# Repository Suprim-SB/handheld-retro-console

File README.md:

# HANDHELD RETRO CONSOLE
A diy handheld retro console that is built to be simple, cheap and small. It includes classic retro games that you can play to spend your time!
<br> 
<br>
<br>

# WHAT IS IT?
A handheld console is a game device meant to fit in the palm of your hands!. Although they are not as powerful as traditional consoles, they are quite nice to help you pass your free time instead of just doomscrolling. And with how everyone larps "anti-brainrot edcs", this project could fit right in :> This handheld console packs enough punch to handle classic retro games like snake, Tetris, brick breaker, Pacman and so on. It includes a 1.3 inch monochrome oled screen to view your games. Its intended feature is supposed to be a compact device you can carry with you anywhere. It also includes a rechargable battery so no hassle of replacing batteries everytime the battery dies.
<br>
<br>_This build of the console includes Snake, Tetris, Pacman, Brickbreaker and a Traffic racer (More games can be added on your own)._
# WHY?
This project was made to be the project for the week 5 of Hack Club half life. It is my first time creating a project trying to learn on my own without following a tutorial word for word. It helped me understand Kicad and project making more.

# WHAT YOU NEED
Despite the project sounding complicated its not that complicated. Since this is a simplified version of the project with a oled instead of tft and less buttons and no speakers (to fit budget and size constraints), this does require a long list of expensive materials.
MATERIALS YOU NEED:
1. ESP32-C3 Supermini (The main microprocessor)
2. 1.3" Oled SH1106 (The display for the game)
3. 6 Tactile Push Buttons (6mmx6mm) (The four directional input and two action buttons)
4. 220Ω Ohm Resistor
5. Protected TP4506 charging module (The battery charger)
6. 6x Push button caps
7. Slide Switch (to turn on and off the console)
8. A 3.7v LiPo Battery pouch (The battery; for this build I was only able to find a 1100MaH battery, but you can use one with higher capacity)

# How the parts fit:
The ESP32-C3 supermini is the main brains of the project. It is what controls the display, loads the games, and takes your inputs. The 1.3" Oled is the display. It shows you the boot animation, the game menu, and displays the games while you play them. The buzzer plays different frequencies depending on what is happening to make the console more polished and fun to use. The tactile input switches are to select the game you want to play from the menu and to control the game. The battery and charging modules are just a part of the module that powers the console.

# Project Status
Designing Phase is complete. The physical board is yet to be made, tested , and shipped.
The PCB design, firmware, Schematics, Gerber Files and the BOM are uploaded here.
<br>_Further changes to the modes, features and designs could be added later_

# Project Photos:
PCB:
<br>
<br>

<br>Schematic:
<br>

## Bill of Materials (BOM)

| Item | Qty | Supplier | Cost/Item | Total Cost | Link |
|---|---:|---|---:|---:|---|
| ESP32-C3-Supermini | 1 | Ekaithau | $4.65 | $4.65 | [Link](https://ekaithau.com/products/esp32-c3-mini/) |
| 1.3" OLED | 1 | Himalayan Solutions | $4.00 | $4.00 | [Link](https://himalayansolution.com/product/1-3-inch-oled-display) |
| Buzzer | 1 | Himalayan Solutions | $0.20 | $0.20 | [Link](https://himalayansolution.com/product/buzzer) |
| LiPo Battery 3.7V | 1 | Giga Nepal | $3.66 | $3.66 | [Link](https://www.giganepal.com/product/3-7v-1100mah-li-po-rechargeable-battery-original-type/) |
| TP4056 Module | 1 | Himalayan Solutions | $0.33 | $0.33 | [Link](https://himalayansolution.com/product/type-c-5v-1a-tp4056-1s-lithium-battery-charger) |
| Push Buttons (5 pack) | 2 | Giga Nepal | $0.66 | $1.32 | [Link](https://www.giganepal.com/product/push-button-switch/) |
| Slide Switch | 1 | Himalayan Solutions | $0.10 | $0.10 | [Link](https://himalayansolution.com/product/slide-switch-small) |
| PCB Printing | 1 | JLCPCB | $2.00 | $2.00 | [Link](https://cart.jlcpcb.com/shopcart/cart/) |
| Passive Components | 3 | Himalayan Solutions | $0.22 | $0.66 | [Link](https://himalayansolution.com/product/capacitor-solid-state-100uf-35v) |
| Estimated Shipping | 1 | - | - | $14.87 | - |
| **Total** | | | | **$31.79** | |
<br> *The photos of carts are uploaded below*

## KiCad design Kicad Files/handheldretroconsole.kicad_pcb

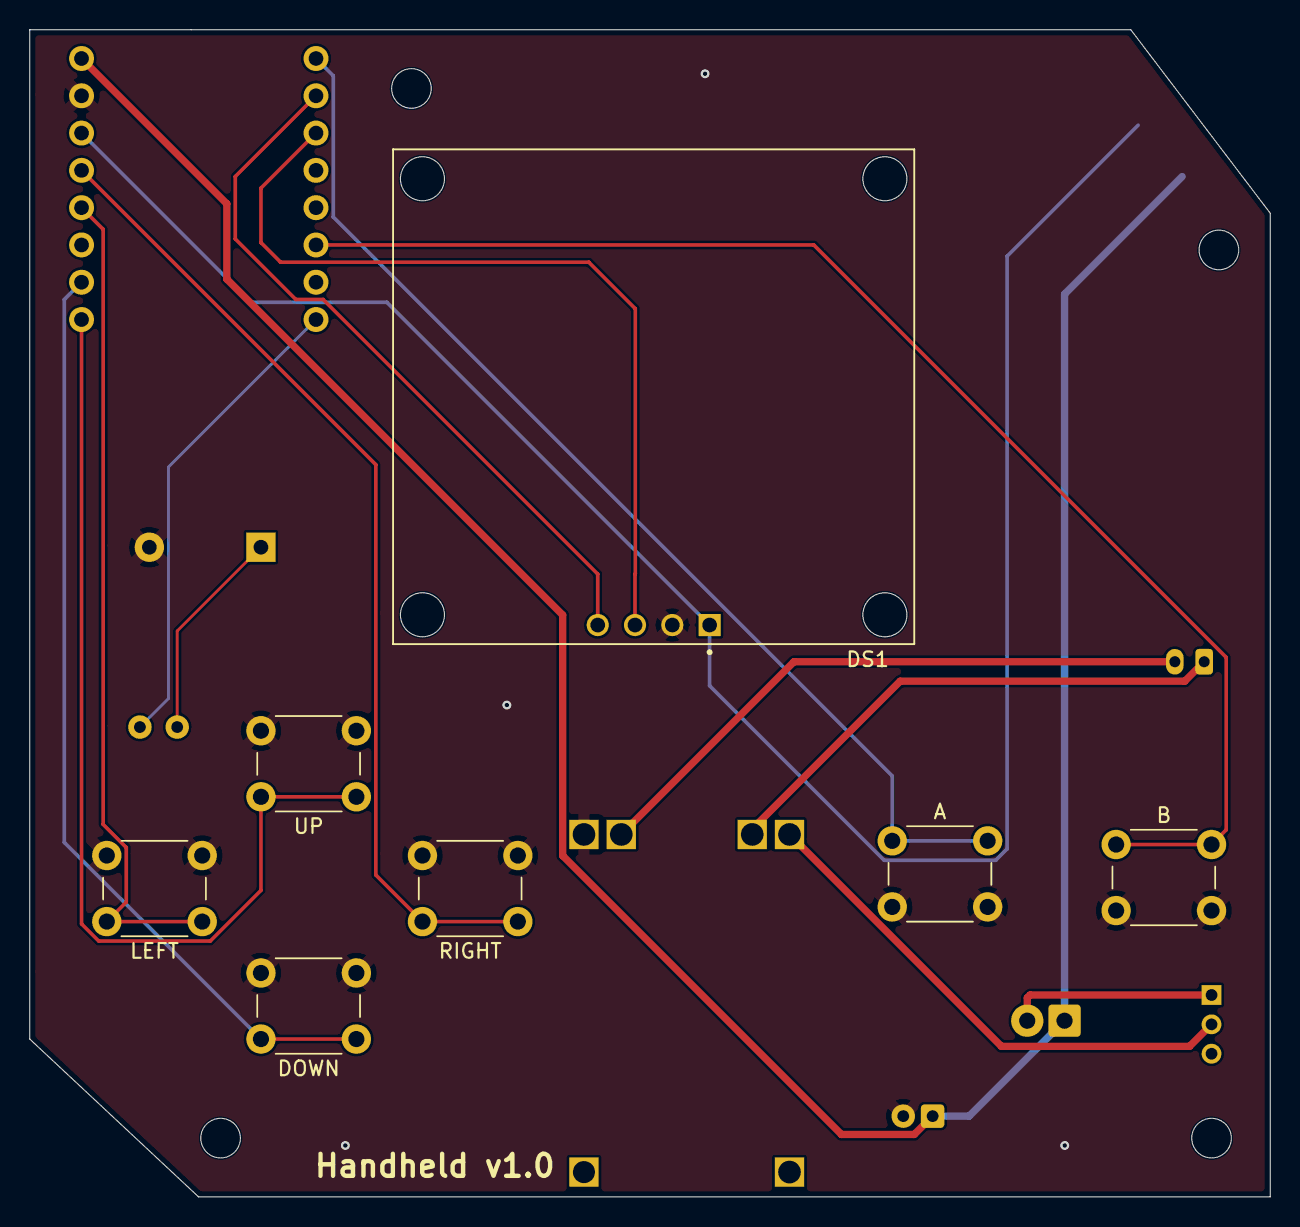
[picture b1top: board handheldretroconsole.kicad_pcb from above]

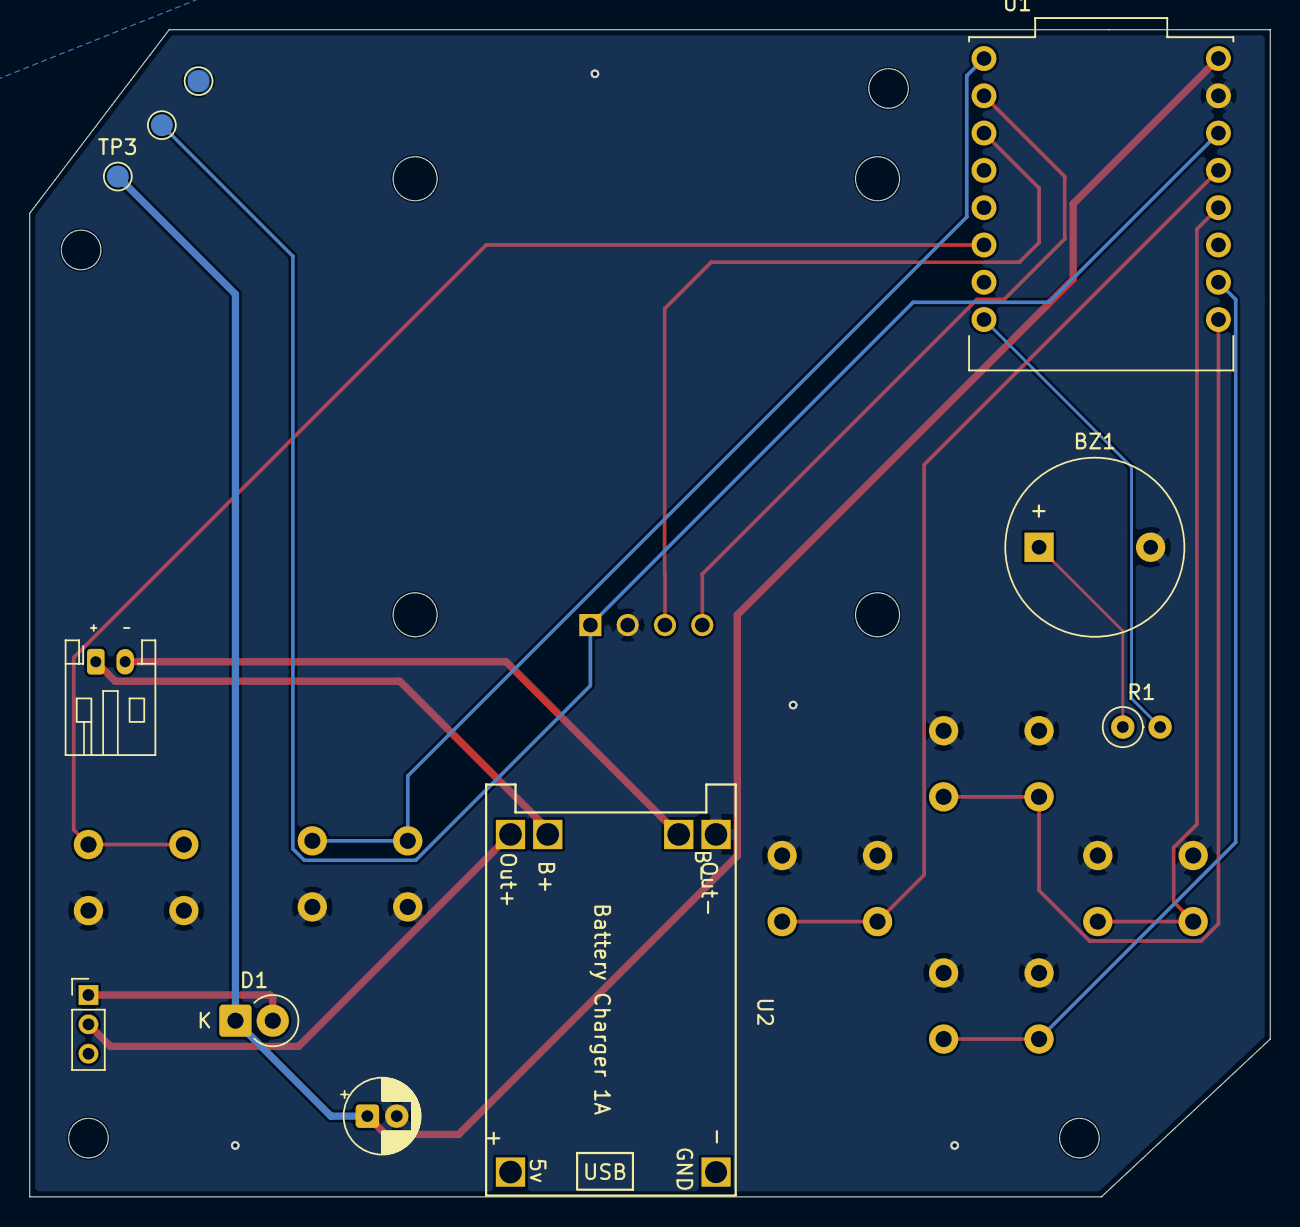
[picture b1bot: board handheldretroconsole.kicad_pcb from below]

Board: 2 copper layers, 84.5 x 79.5 mm, 22 parts (11 on the bottom side), 17 nets.

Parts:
A: SW_Push; SW_PUSH_6mm
B: SW_Push; SW_PUSH_6mm
BZ1: Buzzer; Buzzer_12x9.5RM7.6
C1: C_Polarized; CP_Radial_D5.0mm_P2.00mm
D1: D_Schottky; D_DO-41_SOD81_P2.54mm_Vertical_CathodeUp
DOWN: SW_Push; SW_PUSH_6mm
DS1: OLED_128X64_1.3_I2C; LCD_OLED_128X64_1.3_I2C
H1, H2, H3, H4: MountingHole; MountingHole_2.7mm_M2.5
J1: Battery; JST_PH_S2B-PH-K_1x02_P2.00mm_Horizontal
LEFT: SW_Push; SW_PUSH_6mm
R1: 220; R_Axial_DIN0207_L6.3mm_D2.5mm_P2.54mm_Vertical
RIGHT: SW_Push; SW_PUSH_6mm
SW7: Power; PinHeader_1x03_P2.00mm_Vertical
TP1: GND; TestPoint_Pad_D1.5mm
TP2: +3V3; TestPoint_Pad_D1.5mm
TP3: VSYS; TestPoint_Pad_D1.5mm
U1: ESP32-C3_SUPERMINI_SMD; MODULE_ESP32-C3_SUPERMINI
U2: TP4056_Protected_USBC; TP4056_module
UP: SW_Push; SW_PUSH_6mm

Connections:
+3V3: DS1.1 (VCC), TP2.1 (1_1), U1.3.3 (3V3)
/BTN_A: A.1, U1.5 (GPIO5)
/BTN_B: B.1, U1.10 (GPIO10)
/BTN_DOWN: DOWN.1, U1.1 (GPIO1)
/BTN_LEFT: LEFT.1, U1.3 (GPIO3)
/BTN_RIGHT: RIGHT.1, U1.4 (GPIO4)
/BTN_UP: U1.0 (GPIO0), UP.1
/BUZZER: R1.2, U1.21 (GPIO21)
/I2C_SCL: DS1.3 (SCL), U1.7 (GPIO7)
/I2C_SDA: DS1.4 (SDA), U1.6 (GPIO6)
/VSYS: C1.1, D1.1 (K), TP3.1 (1_1), U1.5V
GND: A.2, B.2, BZ1.2 (-), C1.2, DOWN.2, DS1.2 (GND), LEFT.2, RIGHT.2, TP1.1 (1_1), U1.G (GND), U2.4 (OUT-), UP.2
unnamed: BZ1.1 (+), R1.1
unnamed: D1.2 (A), SW7.1 (A)
unnamed: J1.1, U2.5 (B+)
unnamed: J1.2, U2.6 (B-)
unnamed: SW7.2 (B), U2.3 (OUT+)

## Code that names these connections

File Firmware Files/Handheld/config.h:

#pragma once
#include <Arduino.h>

//  If you ever need move a wire on the PCB, this is the only file you have to edit

// ---------- Debug output ----------
// 1 = print to the Serial Monitor (needs the USB cable plugged in)
// 0 = no serial output at all (use this for battery-powered runs)
#define DEBUG_SERIAL 1

#if DEBUG_SERIAL
  #define LOG(x)    Serial.print(x)
  #define LOGLN(x)  Serial.println(x)
  #define LOGF(...) Serial.printf(__VA_ARGS__)
#else
  #define LOG(x)    do {} while (0)
  #define LOGLN(x)  do {} while (0)
  #define LOGF(...) do {} while (0)
#endif

#define ARRAY_LEN(a) (sizeof(a) / sizeof((a)[0]))

// Pin map (matches the KiCad schematic)
namespace Pin {
  constexpr uint8_t Up     = 0;    // BTN_UP
  constexpr uint8_t Down   = 1;    // BTN_DOWN
  constexpr uint8_t Left   = 3;    // BTN_LEFT
  constexpr uint8_t Right  = 4;    // BTN_RIGHT
  constexpr uint8_t BtnA   = 5;    // BTN_A
  constexpr uint8_t BtnB   = 10;   // BTN_B

  constexpr uint8_t Sda    = 6;    // I2C_SDA 
  constexpr uint8_t Scl    = 7;    // I2C_SCL  

  constexpr uint8_t Buzzer = 21;   // BUZZER (through the 220 ohm resistor)
}

// Display
constexpr uint8_t  SCREEN_W  = 128;
constexpr uint8_t  SCREEN_H  = 64;
constexpr uint8_t  OLED_ADDR = 0x3C;     
constexpr uint32_t I2C_HZ    = 400000;   

// ---------- Buttons ----------
constexpr uint8_t  DEBOUNCE_MS  = 12;   
constexpr uint16_t EXIT_HOLD_MS = 5000;  // hold B this long inside a game to go back to the menu (I put 5 seconds since that should be good enough)

// ---------- Games ----------
constexpr uint8_t GAME_COUNT = 5;
